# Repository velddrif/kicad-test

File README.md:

# KiCAD & KiBOT Test Repo

## Figure 1

## Figure 2

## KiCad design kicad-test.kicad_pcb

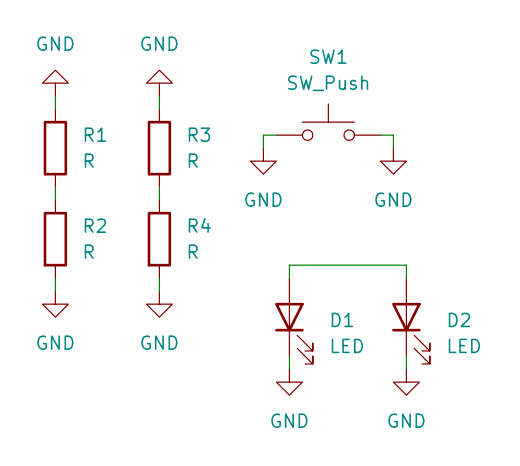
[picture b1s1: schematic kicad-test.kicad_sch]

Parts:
D1, D2: LED; LED_1210_3225Metric
R1, R2, R3, R4: R; R_1206_3216Metric
SW1: SW_Push; SW_PUSH_6mm_H8mm

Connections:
GND: D1.1 (K), D2.1 (K), R1.1, R2.2, R3.1, R4.2, SW1.1, SW1.2
unnamed: D1.2 (A), D2.2 (A)
unnamed: R1.2, R2.1
unnamed: R3.2, R4.1

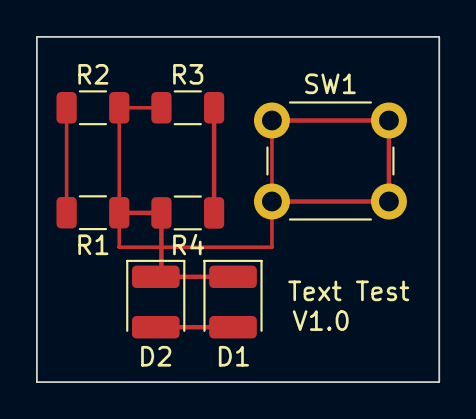
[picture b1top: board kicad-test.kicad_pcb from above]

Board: 2 copper layers, 22.4 x 19.2 mm, 7 parts (0 on the bottom side), 4 nets.

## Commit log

2024-01-12 added yaml
2024-01-12 added kibot config file
2024-01-12 changed kibot command
2024-01-12 added two extra resistors
2024-01-12 updated readme to always show the most up to date pcb image
2024-01-12 added button
2024-01-13 added two leds
2024-01-13 Added more images to README.md
